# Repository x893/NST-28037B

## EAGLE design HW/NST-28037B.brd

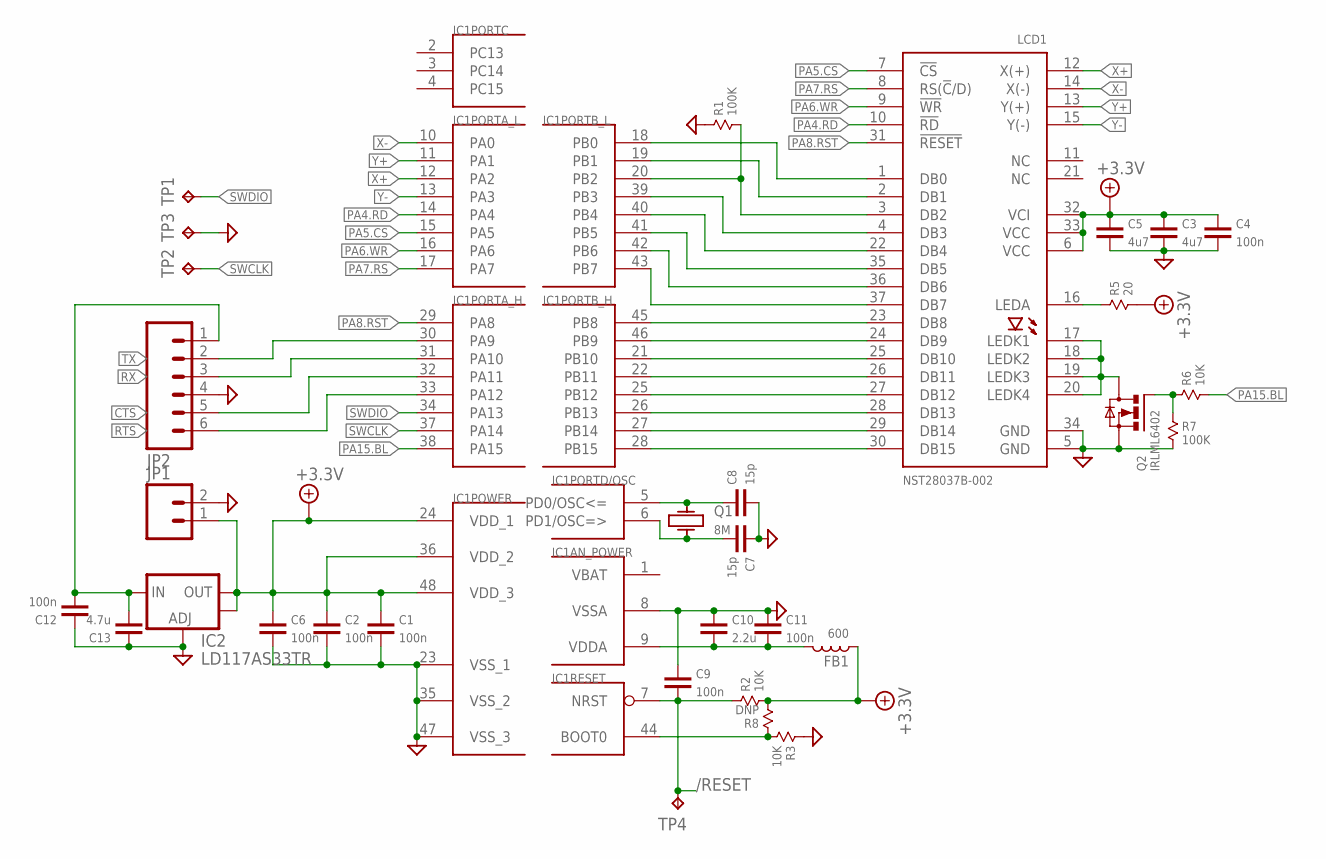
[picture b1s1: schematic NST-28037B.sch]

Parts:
C1, C2, C4, C6, C9, C11, C12: 100n; 0603
C3, C5: 4u7; 0603
C7, C8: 15p; 0603
C10: 2.2u; 0603
C13: 4.7u; 0603
FB1: 600; 0603
IC1: STM32F10XCXT6; TQFP48
IC2: LD117AS33TR; SOT223
JP1: M02PTH; 1X02
JP2: M06SIP; 1X06
LCD1: NST28037B-002
Q1: 8M; KX-9A
Q2: IRLML6402; SOT-23
R1, R7: 100K; 0603
R2, R3, R6: 10K; 0603
R5: 20; 0805
R8: DNP; 0603
TP1, TP2, TP3, TP4: TPTP12R; TP12R

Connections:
+3.3V: C1.2, C2.2, C3.2, C4.2, C5.2, C6.2, FB1.1, IC1.24 (VDD_1), IC1.36 (VDD_2), IC1.48 (VDD_3), IC2.2 (OUT), IC2.4 (OUT), JP1.1, LCD1.6 (VCC), LCD1.32 (VCI), LCD1.33 (VCC), R2.2, R5.2, R8.2
/RESET: C9.1, IC1.7 (NRST), R2.1, TP4.TP
CTS: IC1.32 (PA11), JP2.5
D0: IC1.18 (PB0), LCD1.1 (DB0)
D1: IC1.19 (PB1), LCD1.2 (DB1)
D2: IC1.20 (PB2), LCD1.3 (DB2), R1.2
D3: IC1.39 (PB3), LCD1.4 (DB3)
D4: IC1.40 (PB4), LCD1.22 (DB4)
D5: IC1.41 (PB5), LCD1.35 (DB5)
D6: IC1.42 (PB6), LCD1.36 (DB6)
D7: IC1.43 (PB7), LCD1.37 (DB7)
D8: IC1.45 (PB8), LCD1.23 (DB8)
D9: IC1.46 (PB9), LCD1.24 (DB9)
D10: IC1.21 (PB10), LCD1.25 (DB10)
D11: IC1.22 (PB11), LCD1.26 (DB11)
D12: IC1.25 (PB12), LCD1.27 (DB12)
D13: IC1.26 (PB13), LCD1.28 (DB13)
D14: IC1.27 (PB14), LCD1.29 (DB14)
D15: IC1.28 (PB15), LCD1.30 (DB15)
GND: C1.1, C2.1, C3.1, C4.1, C5.1, C6.1, C7.2, C8.1, C9.2, C10.2, C11.2, C12.2, C13.2, IC1.8 (VSSA), IC1.23 (VSS_1), IC1.35 (VSS_2), IC1.47 (VSS_3), IC2.1 (ADJ), JP1.2, JP2.4, LCD1.5 (GND), LCD1.34 (GND), Q2.2 (S), R1.1, R3.1, R7.2, TP3.TP
LEDA-1: LCD1.16 (LEDA), R5.1
LEDK: LCD1.17 (LEDK1), LCD1.18 (LEDK2), LCD1.19 (LEDK3), LCD1.20 (LEDK4), Q2.3 (D)
unnamed: C8.2, IC1.5 (PD0/OSC<=), Q1.1
unnamed: C7.1, IC1.6 (PD1/OSC=>), Q1.3 (2)
unnamed: Q2.1 (G), R6.1, R7.1
unnamed: C10.1, C11.1, FB1.2, IC1.9 (VDDA)
unnamed: IC1.44 (BOOT0), R3.2, R8.1
PA4.RD: IC1.14 (PA4), LCD1.10 (!RD)
PA5.CS: IC1.15 (PA5), LCD1.7 (!CS)
PA6.WR: IC1.16 (PA6), LCD1.9 (!WR)
PA7.RS: IC1.17 (PA7), LCD1.8 (RS(!C!/D))
PA8.RST: IC1.29 (PA8), LCD1.31 (!RESET)
PA15.BL: IC1.38 (PA15), R6.2
RTS: IC1.33 (PA12), JP2.6
RX: IC1.31 (PA10), JP2.3
SWCLK: IC1.37 (PA14), TP2.TP
SWDIO: IC1.34 (PA13), TP1.TP
TX: IC1.30 (PA9), JP2.2
VBAT: IC1.1 (VBAT)
VIN: C12.1, C13.1, IC2.3 (IN), JP2.1
X+: IC1.12 (PA2), LCD1.12 (X(+))
X-: IC1.10 (PA0), LCD1.14 (X(-))
Y+: IC1.11 (PA1), LCD1.13 (Y(+))
Y-: IC1.13 (PA3), LCD1.15 (Y(-))

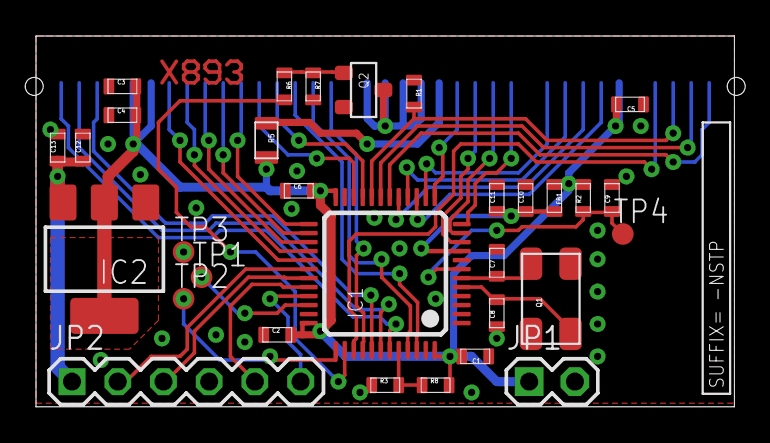
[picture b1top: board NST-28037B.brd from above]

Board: 2 copper layers, 38.8 x 20.6 mm, 33 parts (1 on the bottom side), 43 nets.

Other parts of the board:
U$1: -NSTP; SUFFIX

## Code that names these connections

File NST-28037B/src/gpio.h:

//*** <<< Use Configuration Wizard in Context Menu >>> ***
#ifndef __X893_GPIO_H__
#define __X893_GPIO_H__

#include "stm32f10x.h"

#define PA0		0
#define PA1		1
#define PA2		2
#define PA3		3
#define PA4		4
#define PA5		5
#define PA6		6
#define PA7		7
#define PA8		8
#define PA9		9
#define PA10	10
#define PA11	11
#define PA12	12
#define PA13	13
#define PA14	14
#define PA15	15

#define PB0		16
#define PB1		17
#define PB2		18
#define PB3		19
#define PB4		20
#define PB5		21
#define PB6		22
#define PB7		23
#define PB8		24
#define PB9		25
#define PB10	26
#define PB11	27
#define PB12	28
#define PB13	29
#define PB14	30
#define PB15	31

typedef unsigned char PinMode_Type;

#if defined( STM32F2XX ) || defined( STM32F4XX )

	#define PinMode_AIn			(PinMode_Type)(GPIO_Mode_AIN)
	#define PinMode_In			(PinMode_Type)(GPIO_Mode_IN  | (GPIO_PuPd_NOPULL << 2))
	#define PinMode_In_PD		(PinMode_Type)(GPIO_Mode_IN  | (GPIO_PuPd_DOWN   << 2))
	#define PinMode_In_PU		(PinMode_Type)(GPIO_Mode_IN  | (GPIO_PuPd_UP     << 2))

	#define PinMode_Out_OD		PinMode_Out_OD_50M
	#define PinMode_Out_OD_2M	(PinMode_Type)(GPIO_Mode_OUT | (GPIO_OType_OD << 6) | (GPIO_Speed_2MHz   << 4))
	#define PinMode_Out_OD_10M	(PinMode_Type)(GPIO_Mode_OUT | (GPIO_OType_OD << 6) | (GPIO_Speed_10MHz  << 4))
	#define PinMode_Out_OD_50M	(PinMode_Type)(GPIO_Mode_OUT | (GPIO_OType_OD << 6) | (GPIO_Speed_50MHz  << 4))
	#define PinMode_Out_OD_100M	(PinMode_Type)(GPIO_Mode_OUT | (GPIO_OType_OD << 6) | (GPIO_Speed_100MHz << 4))

	#define PinMode_Out_PP		PinMode_Out_PP_50M
	#define PinMode_Out_PP_2M	(PinMode_Type)(GPIO_Mode_OUT | (GPIO_OType_PP << 6) | (GPIO_Speed_2MHz   << 4))
	#define PinMode_Out_PP_10M	(PinMode_Type)(GPIO_Mode_OUT | (GPIO_OType_PP << 6) | (GPIO_Speed_10MHz  << 4))
	#define PinMode_Out_PP_50M	(PinMode_Type)(GPIO_Mode_OUT | (GPIO_OType_PP << 6) | (GPIO_Speed_50MHz  << 4))
	#define PinMode_Out_PP_100M	(PinMode_Type)(GPIO_Mode_OUT | (GPIO_OType_PP << 6) | (GPIO_Speed_100MHz << 4))
	
	#define PinMode_AF_OD		(PinMode_Type)(GPIO_Mode_AF  | (GPIO_OType_OD << 6) | (GPIO_Speed_50MHz  << 4))

	#define PinMode_AF_PP		PinMode_AF_PP_50M
	#define PinMode_AF_PP_2M	(PinMode_Type)(GPIO_Mode_AF  | (GPIO_OType_PP << 6) | (GPIO_Speed_2MHz   << 4))
	#define PinMode_AF_PP_10M	(PinMode_Type)(GPIO_Mode_AF  | (GPIO_OType_PP << 6) | (GPIO_Speed_10MHz  << 4))
	#define PinMode_AF_PP_50M	(PinMode_Type)(GPIO_Mode_AF  | (GPIO_OType_PP << 6) | (GPIO_Speed_50MHz  << 4))
	#define PinMode_AF_PP_100M	(PinMode_Type)(GPIO_Mode_AF  | (GPIO_OType_PP << 6) | (GPIO_Speed_100MHz << 4))
	
	#define PinMode_AF_PP_PU	(PinMode_Type)(GPIO_Mode_AF  | (GPIO_OType_PP << 6) | (GPIO_PuPd_UP << 2) | (GPIO_Speed_50MHz  << 4))

#elif defined( STM32F10X_HD ) || defined( STM32F10X_LD_VL )

	#define PinMode_AIn			(PinMode_Type)(GPIO_Mode_AIN)
	#define PinMode_In			(PinMode_Type)(GPIO_Mode_IN_FLOATING)
	#define PinMode_In_PD		(PinMode_Type)(GPIO_Mode_IPD)
	#define PinMode_In_PU		(PinMode_Type)(GPIO_Mode_IPU)

	#define PinMode_Out_OD		PinMode_Out_OD_50M
	#define PinMode_Out_OD_2M	(PinMode_Type)(GPIO_Mode_Out_OD | GPIO_Speed_2MHz)
	#define PinMode_Out_OD_10M	(PinMode_Type)(GPIO_Mode_Out_OD | GPIO_Speed_10MHz)
	#define PinMode_Out_OD_50M	(PinMode_Type)(GPIO_Mode_Out_OD | GPIO_Speed_50MHz)

	#define PinMode_Out_PP		PinMode_Out_PP_50M
	#define PinMode_Out_PP_2M	(PinMode_Type)(GPIO_Mode_Out_PP | GPIO_Speed_2MHz)
	#define PinMode_Out_PP_10M	(PinMode_Type)(GPIO_Mode_Out_PP | GPIO_Speed_10MHz)
	#define PinMode_Out_PP_50M	(PinMode_Type)(GPIO_Mode_Out_PP | GPIO_Speed_50MHz)

	#define PinMode_AF_OD		(PinMode_Type)(GPIO_Mode_AF_OD  | GPIO_Speed_50MHz)
	#define PinMode_AF_PP		(PinMode_Type)(GPIO_Mode_AF_PP  | GPIO_Speed_50MHz)

#else
	#error "CPU type not define"
#endif

void	pinMode		(uint8_t pin, PinMode_Type mode);
void	pinLow		(uint8_t pin);
void	pinHigh		(uint8_t pin);
void	pinToggle	(uint8_t pin);
uint8_t	pinRead		(uint8_t pin);
void	pinRemap	(uint8_t pin, uint8_t GPIO_AF);

#endif
